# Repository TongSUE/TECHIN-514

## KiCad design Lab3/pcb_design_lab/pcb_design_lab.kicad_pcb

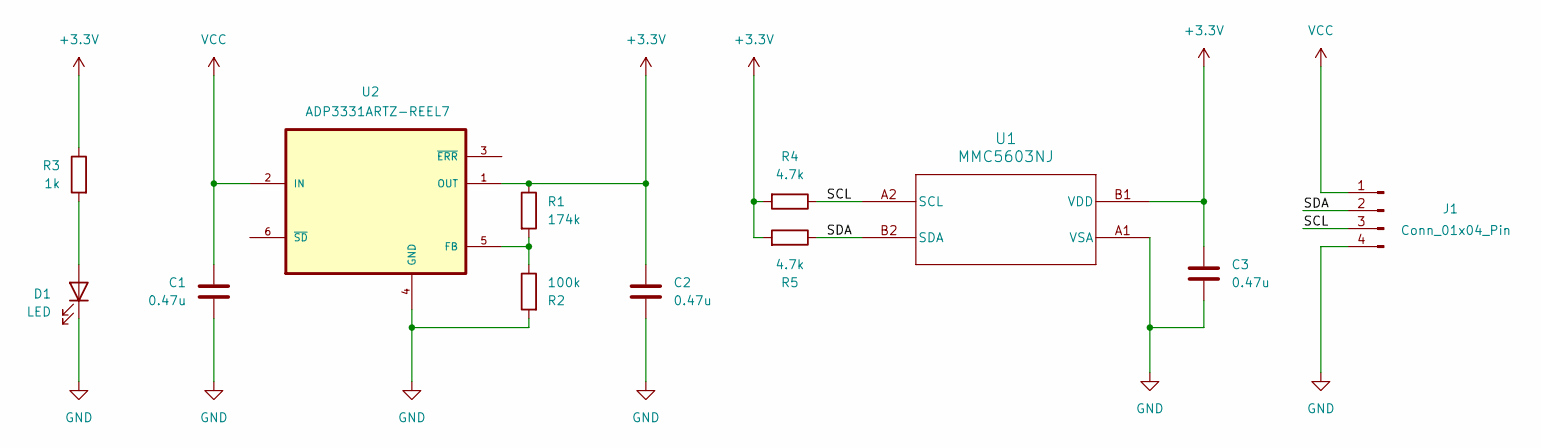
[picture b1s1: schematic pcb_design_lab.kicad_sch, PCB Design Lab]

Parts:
C1, C2, C3: 0.47u; C_0402_1005Metric_Pad0.74x0.62mm_HandSolder
D1: LED; LED_0402_1005Metric
J1: Conn_01x04_Pin; PinSocket_1x04_P2.54mm_Vertical
R1: 174k; R_0402_1005Metric_Pad0.72x0.64mm_HandSolder
R2: 100k; R_0402_1005Metric_Pad0.72x0.64mm_HandSolder
R3: 1k; R_0402_1005Metric_Pad0.72x0.64mm_HandSolder
R4, R5: 4.7k; R_0402_1005Metric_Pad0.72x0.64mm_HandSolder
U1: MMC5603NJ; WLP4_0P82X0P82_MEM
U2: ADP3331ARTZ-REEL7; SOT95P280X145-6N

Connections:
+3.3V: C2.1, C3.1, R1.1, R3.1, R4.2, R5.2, U1.B1 (VDD), U2.1 (OUT)
/SCL: J1.3, R4.1, U1.A2 (SCL)
/SDA: J1.2, R5.1, U1.B2 (SDA)
GND: C1.1, C2.2, C3.2, D1.1 (K), J1.4, R2.2, U1.A1 (VSA), U2.4 (GND)
unnamed: D1.2 (A), R3.2
unnamed: R1.2, R2.1, U2.5 (FB)
VCC: C1.2, J1.1, U2.2 (IN)

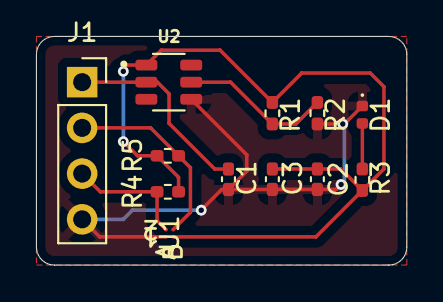
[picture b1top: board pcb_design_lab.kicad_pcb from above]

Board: 2 copper layers, 20.6 x 12.7 mm, 12 parts (0 on the bottom side), 7 nets.

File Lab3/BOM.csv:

"#","Reference","Qty","Value","Footprint","DNP"
"1","C1, C2, C3","3","0.47u","Capacitor_SMD:C_0402_1005Metric_Pad0.74x0.62mm_HandSolder",""
"2","D1","1","LED","LED_SMD:LED_0402_1005Metric",""
"3","J1","1","Conn_01x04_Pin","Connector_PinSocket_2.54mm:PinSocket_1x04_P2.54mm_Vertical",""
"4","R1","1","174k","Resistor_SMD:R_0402_1005Metric_Pad0.72x0.64mm_HandSolder",""
"5","R2","1","100k","Resistor_SMD:R_0402_1005Metric_Pad0.72x0.64mm_HandSolder",""
"6","R3","1","1k","Resistor_SMD:R_0402_1005Metric_Pad0.72x0.64mm_HandSolder",""
"7","R4, R5","2","4.7k","Resistor_SMD:R_0402_1005Metric_Pad0.72x0.64mm_HandSolder",""
"8","U1","1","MMC5603NJ","MMC5603NJ:WLP4_0P82X0P82_MEM",""
"9","U2","1","ADP3331ARTZ-REEL7","ADP3331:SOT95P280X145-6N",""

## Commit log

2026-01-05 Lab 1
2026-01-05 Upgrade Lab1
2026-01-05 github repo screenshot
2026-01-15 Lab 2
2026-01-26 Lab 4
2026-01-29 Lab 3
2026-01-29 Screenshots and BOM
2026-02-05 Lab 5
